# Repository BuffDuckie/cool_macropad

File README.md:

# Nick's macropad
Hi! I didn't really give this macropad a cool name like DuckiePad and just called it a generic "Nick's Macropad" (I might refer to it as "Cool Macropad" as well). My macropad has 8 keys and a rotary encoder. It uses KMK firmware. It also has 4 LEDS! I'm probably going to use this macropad for gaming or general school-use, and it can double as a desk decoration. 

# Schematic
Here's the schematic of my macropad. Shouldn't be anything too crazy. For more info, you can view the file under the PCB folder.

# PCB
Here's the PCB. The routing probably could have been more optimal as I mostly used KiCad's autorouter, but the PCB is 100 x 100mm and everything (at least electrically) works.

# CAD
I used OnShape for the 3D design instead of Fusion360, but everything still turned out okay. I attached a screenshot of the completed case, and a screenshot of an exploded view. The blank rectangle will be my PCB and has the same dimensions. The third sceenshot is a combined model view of my case and PCB, showing that my case will actually be able to fit my PCB.

# Bill of Materials 
This macropad contains:
- 1x EC11 Rotary Encoder
- 1x XIAO RP2040
- 8x Cherry MX Switches
- 8x DSA Keycaps
- 4x SK6812 MINI-E LEDs
- 4x M3x16mm screws
- 4x M3x5mx4mm heatset inserts
- 1x case (2 parts)

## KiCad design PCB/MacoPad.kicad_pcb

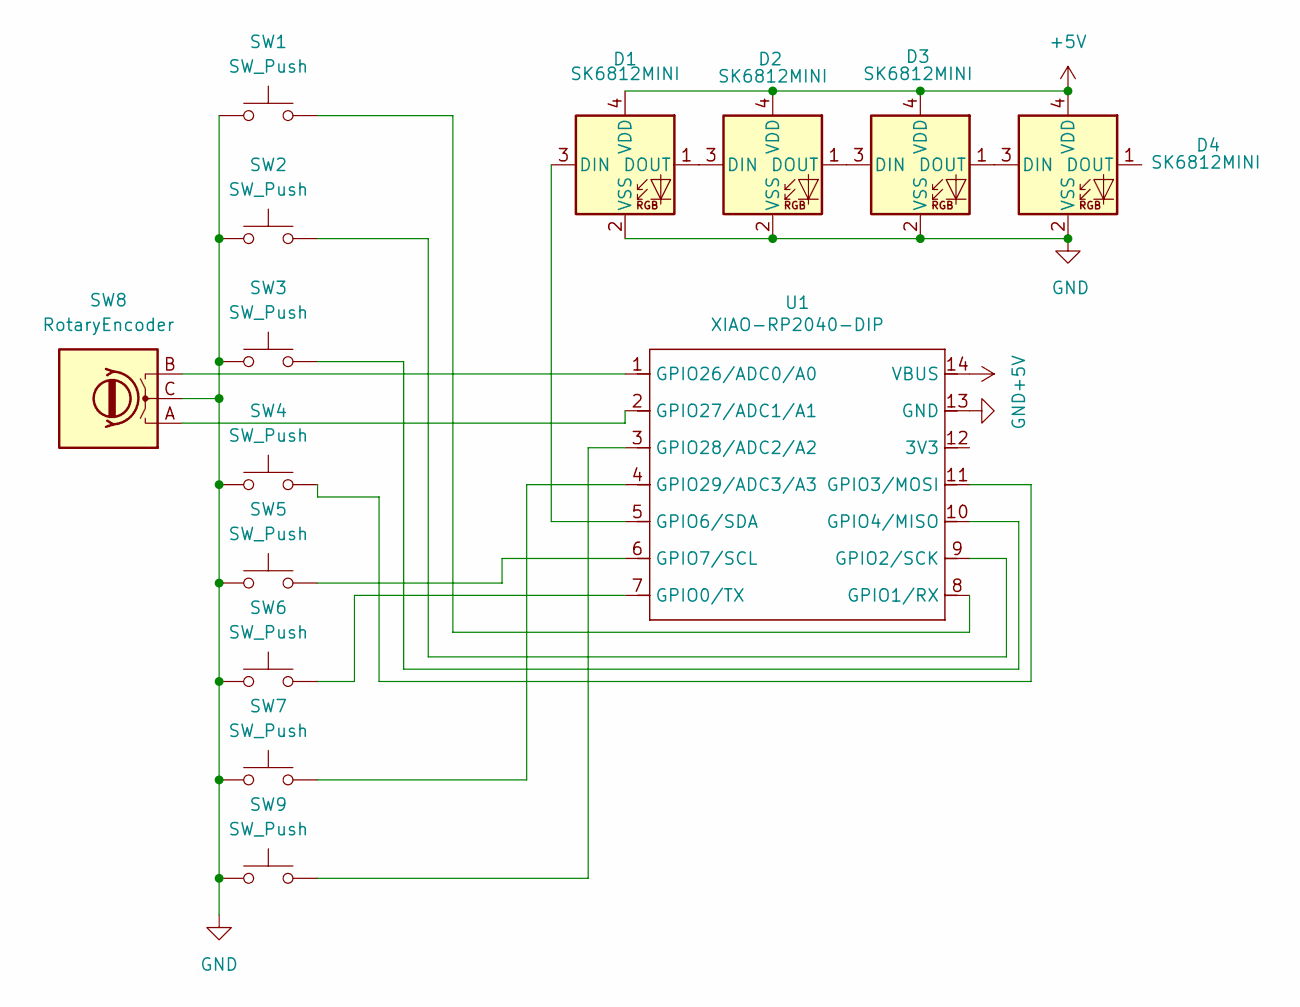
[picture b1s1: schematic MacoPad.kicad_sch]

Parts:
D1, D2, D3, D4: SK6812MINI; LED_SK6812MINI_PLCC4_3.5x3.5mm_P1.75mm
SW1, SW2, SW3, SW4, SW5, SW6, SW7, SW9: SW_Push; SW_Cherry_MX_1.00u_PCB
SW8: RotaryEncoder; RotaryEncoder_Alps_EC11E_Vertical_H20mm
U1: XIAO-RP2040-DIP

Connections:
+5V: D1.4 (VDD), D2.4 (VDD), D3.4 (VDD), D4.4 (VDD), U1.14 (VBUS)
GND: D1.2 (VSS), D2.2 (VSS), D3.2 (VSS), D4.2 (VSS), SW1.1, SW2.1, SW3.1, SW4.1, SW5.1, SW6.1, SW7.1, SW8.C, SW9.1, U1.13 (GND)
unnamed: D1.3 (DIN), U1.5 (GPIO6/SDA)
unnamed: D1.1 (DOUT), D2.3 (DIN)
unnamed: D2.1 (DOUT), D3.3 (DIN)
unnamed: D3.1 (DOUT), D4.3 (DIN)
unnamed: SW6.2, U1.7 (GPIO0/TX)
unnamed: SW1.2, U1.8 (GPIO1/RX)
unnamed: SW2.2, U1.9 (GPIO2/SCK)
unnamed: SW4.2, U1.11 (GPIO3/MOSI)
unnamed: SW3.2, U1.10 (GPIO4/MISO)
unnamed: SW5.2, U1.6 (GPIO7/SCL)
unnamed: SW8.B, U1.1 (GPIO26/ADC0/A0)
unnamed: SW8.A, U1.2 (GPIO27/ADC1/A1)
unnamed: SW9.2, U1.3 (GPIO28/ADC2/A2)
unnamed: SW7.2, U1.4 (GPIO29/ADC3/A3)

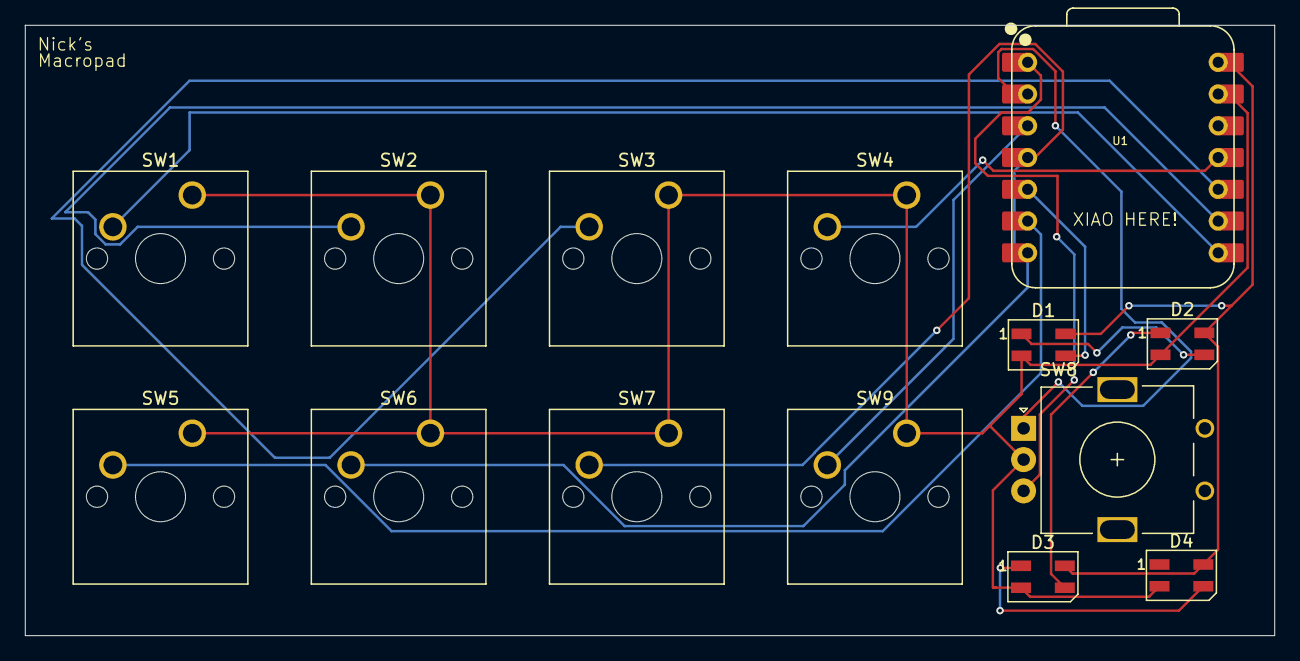
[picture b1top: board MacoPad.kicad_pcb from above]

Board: 2 copper layers, 99.9 x 48.8 mm, 14 parts (0 on the bottom side), 16 nets.

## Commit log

2025-12-23 Add README
2025-12-23 Fix image paths
2025-12-23 Fix Formatting
2025-12-23 Added combined model
